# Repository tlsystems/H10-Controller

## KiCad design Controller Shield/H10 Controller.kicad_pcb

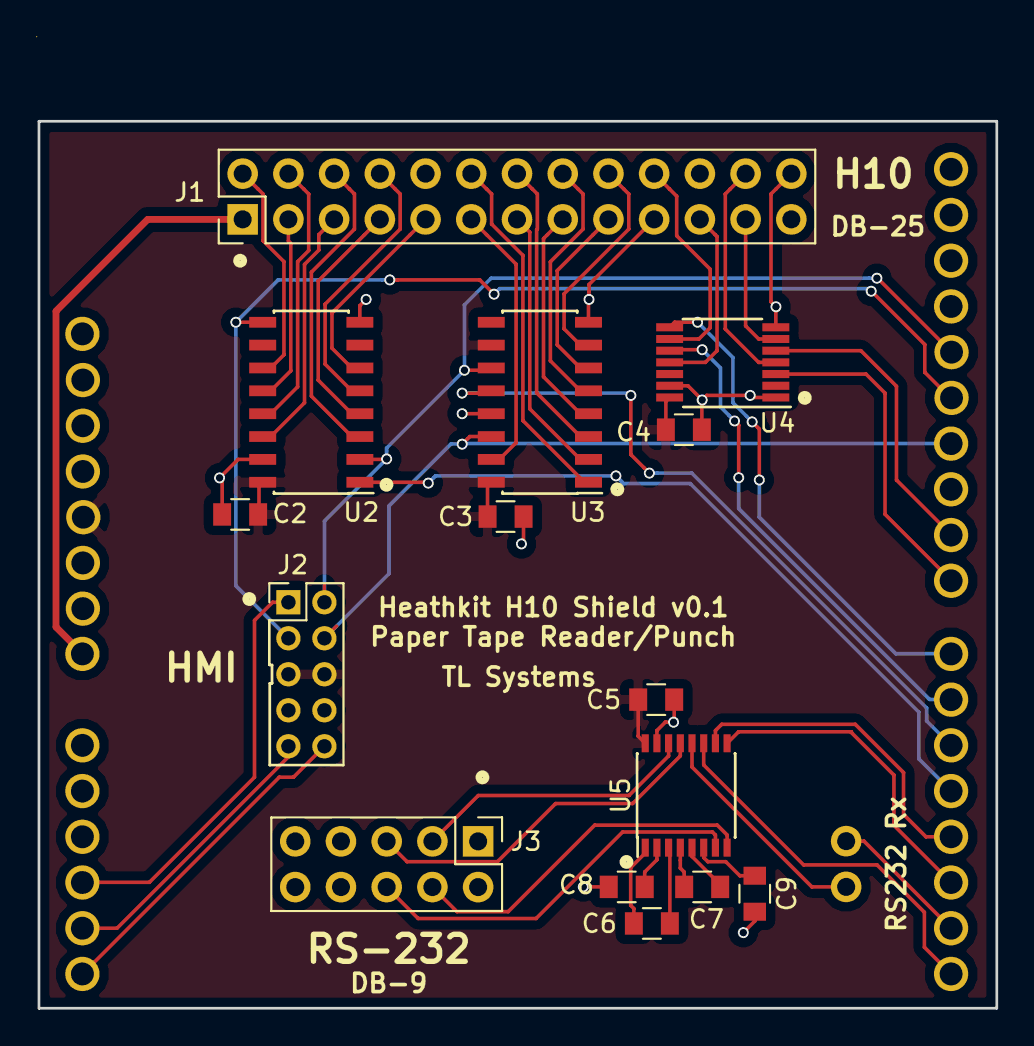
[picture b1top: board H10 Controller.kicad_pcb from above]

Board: 2 copper layers, 53.2 x 49.3 mm, 17 parts (0 on the bottom side), 50 nets.

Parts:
C2, C3, C4, C5, C6, C7, C8, C9: 0.1uF; C_0805
J1: CONN_02X13; Pin_Header_Straight_2x13_Pitch2.54mm
J2: CONN_02X05; Pin_Header_Straight_2x05_Pitch2.00mm
J3: CONN_02X05; Pin_Header_Straight_2x05_Pitch2.54mm
JB1: JumperBlock_2-Pin; Jumper_Block_1x02_2.54mm
U1: ArduinoUno; ArduinoShield
U2: 74HCT165; SOIC-16_3.9x9.9mm_Pitch1.27mm
U3: 74HCT595; SOIC-16_3.9x9.9mm_Pitch1.27mm
U4: 74HCT04; TSSOP-14_4.4x5mm_Pitch0.65mm
U5: MAX3232; SSOP-16_4.4x5.2mm_Pitch0.65mm

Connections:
+12V: J1.1, U1.8
/CTS: U1.17, U5.9
/DispCS: J2.9, U1.13
/DispDC: J2.1, U1.12
/MISO: J2.3, U1.27, U2.9
/MOSI: J2.4, U1.26, U3.14
/PD0: J1.11, U3.15
/PD1: J1.12, U3.1
/PD2: J1.13, U3.2
/PD3: J1.14, U3.3
/PD4: J1.15, U3.4
/PD5: J1.16, U3.5
/PD6: J1.17, U3.6
/PD7: J1.18, U3.7
/PunchDataLatch: U1.20, U3.12
/PunchReady: U1.21, U4.10
/PunchStart: U1.23, U4.3
/RD0: J1.2, U2.11
/RD1: J1.3, U2.12
/RD2: J1.4, U2.13
/RD3: J1.5, U2.14
/RD4: J1.6, U2.3
/RD5: J1.7, U2.4
/RD6: J1.8, U2.5
/RD7: J1.9, U2.6
/RS232_CTS: J3.4, U5.8
/RS232_RTS: J3.6, U5.7
/RS232_RXD: J3.5, U5.13
/RS232_TXD: J3.3, U5.14
/RTS: U1.18, U5.10
/ReaderReady: U1.22, U4.8
/ReaderStart: U1.24, U4.5
/Rx: JB1.2, U1.16
/SCK: J2.2, U1.28, U2.2, U3.11
/Tx: U1.15, U5.11
/~DispRST: J2.10, U1.14
/~PunchReady: J1.21, U4.11
/~PunchStart: J1.24, U4.4
/~ReadDataLoad: U1.19, U2.1
/~ReaderReady: J1.20, U4.9
/~ReaderStart: J1.23, U4.6
GND: C2.2, C3.2, C4.2, C5.2, C8.2, C9.1, J1.10, J1.19, J1.22, J1.26, J2.7, J2.8, J3.9, U1.6, U1.7, U1.29, U2.8, U2.15, U3.8, U3.13, U4.1, U4.7, U4.13, U5.15
unnamed: C6.1, U5.1
unnamed: C6.2, U5.3
unnamed: C7.1, U5.4
unnamed: C7.2, U5.5
unnamed: C8.1, U5.2
unnamed: C9.2, U5.6
unnamed: JB1.1, U5.12
VCC: C2.1, C3.1, C4.1, C5.1, J2.5, J2.6, U1.5, U2.16, U3.10, U3.16, U4.14, U5.16

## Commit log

2018-01-08 Initial Commit Shield Controller v0.1
